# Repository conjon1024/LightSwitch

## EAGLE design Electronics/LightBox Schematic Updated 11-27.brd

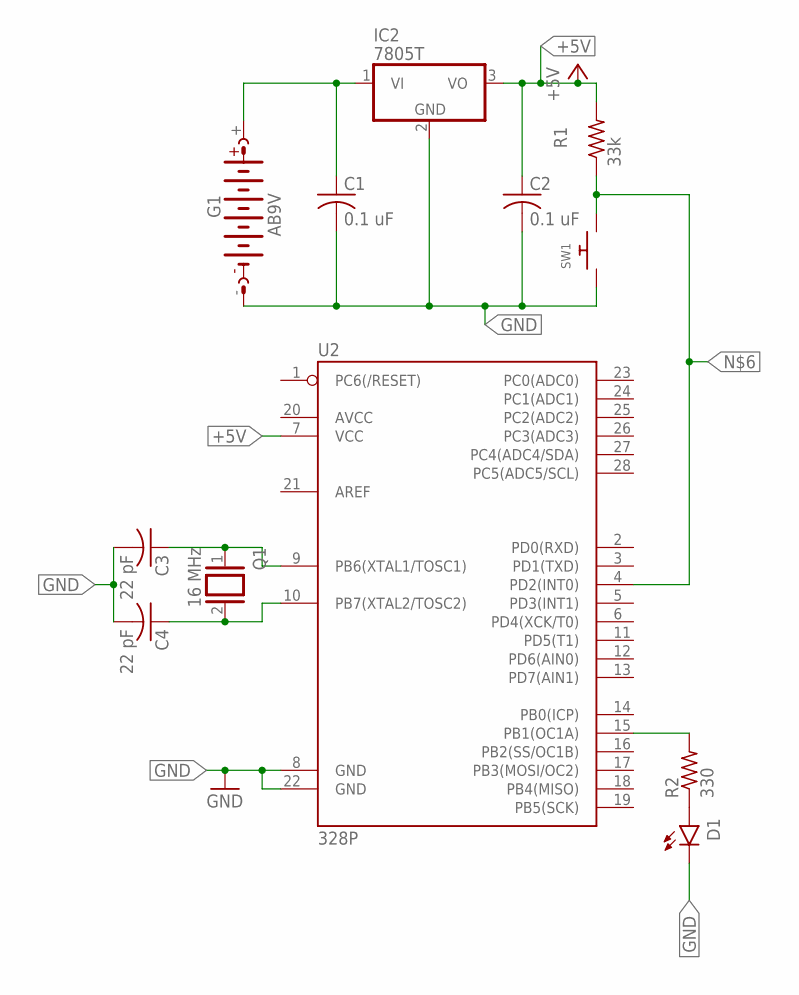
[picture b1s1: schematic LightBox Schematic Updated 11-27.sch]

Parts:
C1, C2: 0.1 uF; C0805
C3, C4: 22 pF; C0805
D1: LED3MM; LED_3MM
G1: AB9V
IC2: 7805T; TO220H
Q1: 16 MHz; QS
R1: 33k; R0805
R2: 330; R0805
SW1: SWITCH_PUSHBUTTONEVQ-PE; TACT_PANA-EVQ
U2: 328P; DIP28

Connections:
+5V: C2.1, IC2.3 (VO), R1.2, U2.7 (VCC)
GND: C1.2, C2.2, C3.2, C4.2, D1.K (C), G1.-, IC2.2 (GND), SW1.P$1, U2.8 (GND), U2.22 (GND)
unnamed: C1.1, G1.+, IC2.1 (VI)
unnamed: R2.2, U2.15 (PB1(OC1A))
unnamed: C4.1, Q1.2, U2.10 (PB7(XTAL2/TOSC2))
unnamed: D1.A, R2.1
unnamed: C3.1, Q1.1, U2.9 (PB6(XTAL1/TOSC1))
unnamed: R1.1, SW1.P$2, U2.4 (PD2(INT0))

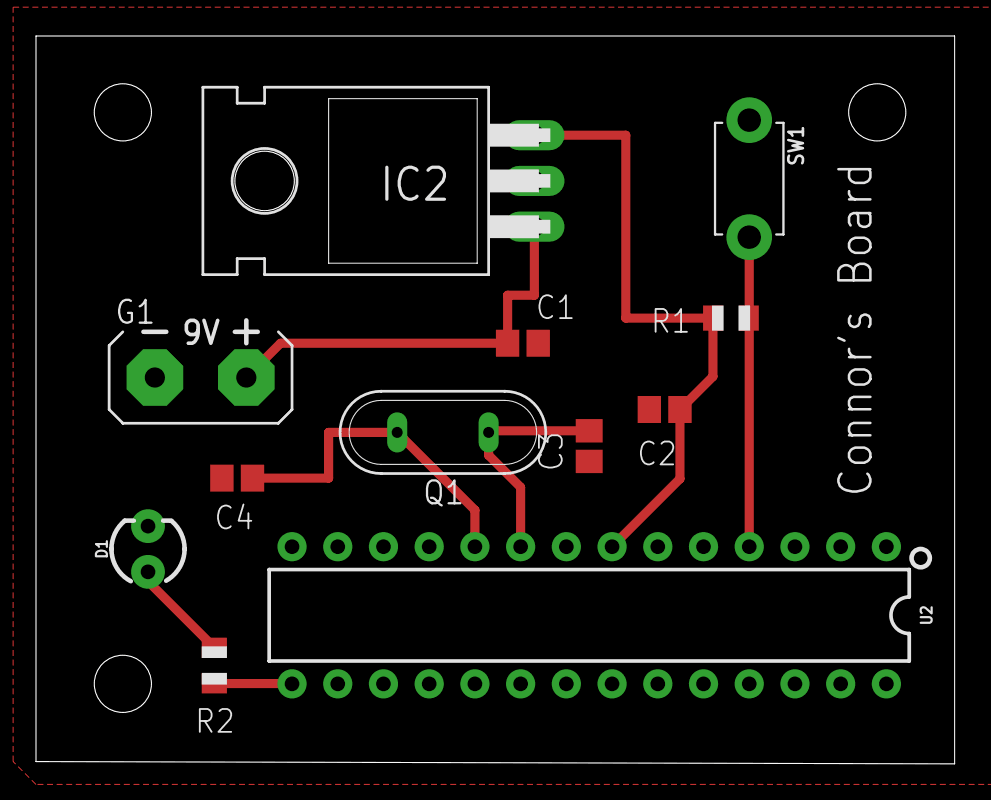
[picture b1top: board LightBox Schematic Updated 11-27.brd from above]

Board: 2 copper layers, 51.0 x 40.4 mm, 12 parts (0 on the bottom side), 8 nets.

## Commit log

2018-10-01 this a test
2018-10-01 remove folder
2018-11-05 Create LightBox Circuit Schematic.jpg
    Prototyping Skills Milestone 03 electronic circuit schematic for the LightBox project.
2018-11-05 Update and rename LightBox Circuit Schematic.jpg to LightBox Circuit Schematic
2018-11-06 Create Software Flowchart
2018-11-12 Create Electronic Design
2018-11-19 Add files via upload
    Updated Circuit Schematic
2018-11-19 Add files via upload
    PCB Layout Top
2018-11-19 Add files via upload
    Lightbox PCB Top Layer
2018-11-19 Add files via upload
    Lightbox PCB Bottom Layer
2018-11-19 Add files via upload
    ECAD Schematic File
2018-11-19 Add files via upload
    ECAD PCB Board File
2018-11-26 Create Documents
2018-12-11 Add files via upload
    The etched board did not end up working, so I was given a new board and re-wired the schematic and soldered the parts onto the board.
2018-12-11 Add files via upload
    This is a video of the working board running through three cycles of each of the five different operating modes.
2018-12-14 Create read

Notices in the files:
parts and their libraries:
SparkFun-LED: Licensing: Creative Commons ShareAlike 4.0 International - https://creativecommons.org/licenses/by-sa/4.0
